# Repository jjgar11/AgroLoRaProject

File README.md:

# Proyecto de Lineas y Antenas 2025-1

## Introduccion

Aca se presenta el codigo necesario para los modulos ESP32 que se encargan de la recepcion y transmision usando dos modulos LoRa.

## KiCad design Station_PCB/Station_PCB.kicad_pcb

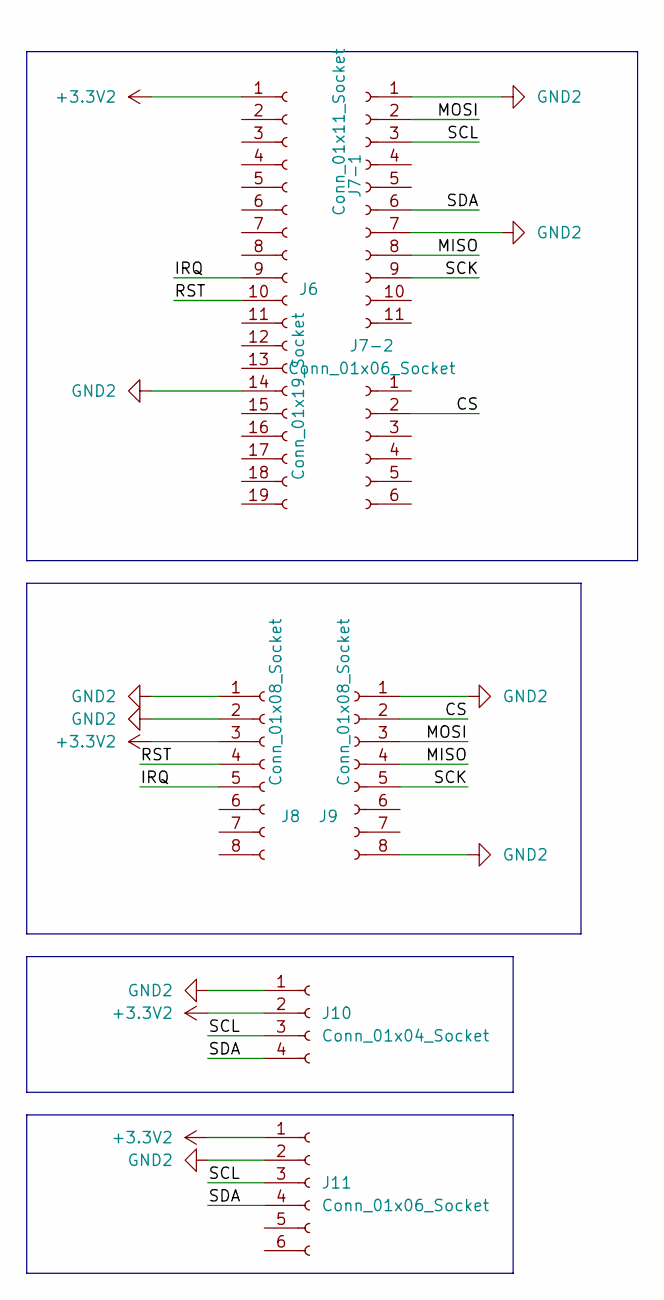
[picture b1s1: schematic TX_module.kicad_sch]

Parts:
J6: Conn_01x19_Socket; PinSocket_1x19_P2.54mm_Vertical
J7-1: Conn_01x11_Socket; PinSocket_1x11_P2.54mm_Vertical
J7-2, J11: Conn_01x06_Socket; PinSocket_1x06_P2.54mm_Vertical
J8, J9: Conn_01x08_Socket; PinSocket_1x08_P2.54mm_Vertical
J10: Conn_01x04_Socket; PinSocket_1x04_P2.54mm_Vertical

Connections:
+3.3V2: J6.1, J8.3, J10.2, J11.1
/TX_module/CS: J7-2.2, J9.2
/TX_module/IRQ: J6.9, J8.5
/TX_module/MISO: J7-1.8, J9.4
/TX_module/MOSI: J7-1.2, J9.3
/TX_module/RST: J6.10, J8.4
/TX_module/SCK: J7-1.9, J9.5
/TX_module/SCL: J7-1.3, J10.3, J11.3
/TX_module/SDA: J7-1.6, J10.4, J11.4
GND2: J6.14, J7-1.1, J7-1.7, J8.1, J8.2, J9.1, J9.8, J10.1, J11.2

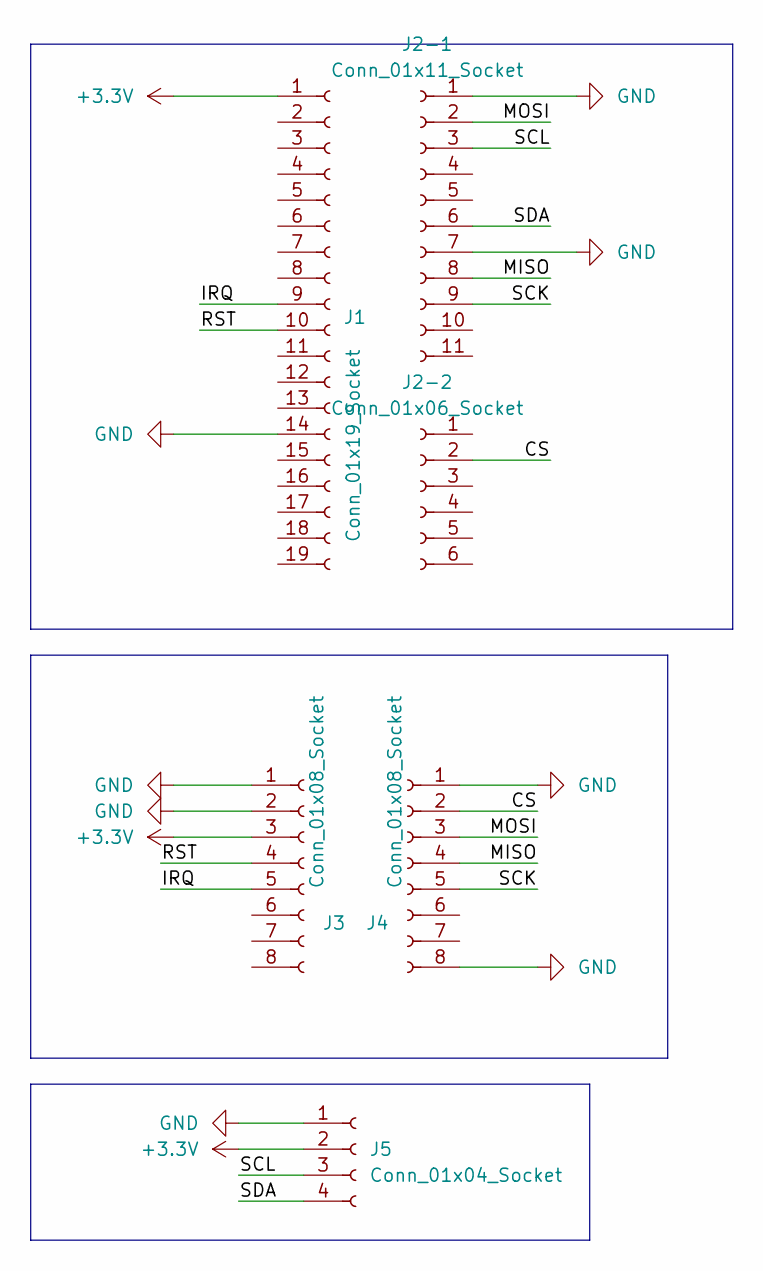
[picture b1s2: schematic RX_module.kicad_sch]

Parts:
J1: Conn_01x19_Socket; PinSocket_1x19_P2.54mm_Vertical
J2-1: Conn_01x11_Socket; PinSocket_1x11_P2.54mm_Vertical
J2-2: Conn_01x06_Socket; PinSocket_1x06_P2.54mm_Vertical
J3, J4: Conn_01x08_Socket; PinSocket_1x08_P2.54mm_Vertical
J5: Conn_01x04_Socket; PinSocket_1x04_P2.54mm_Vertical

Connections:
+3.3V: J1.1, J3.3, J5.2
/RX_module/CS: J2-2.2, J4.2
/RX_module/IRQ: J1.9, J3.5
/RX_module/MISO: J2-1.8, J4.4
/RX_module/MOSI: J2-1.2, J4.3
/RX_module/RST: J1.10, J3.4
/RX_module/SCK: J2-1.9, J4.5
/RX_module/SCL: J2-1.3, J5.3
/RX_module/SDA: J2-1.6, J5.4
GND: J1.14, J2-1.1, J2-1.7, J3.1, J3.2, J4.1, J4.8, J5.1

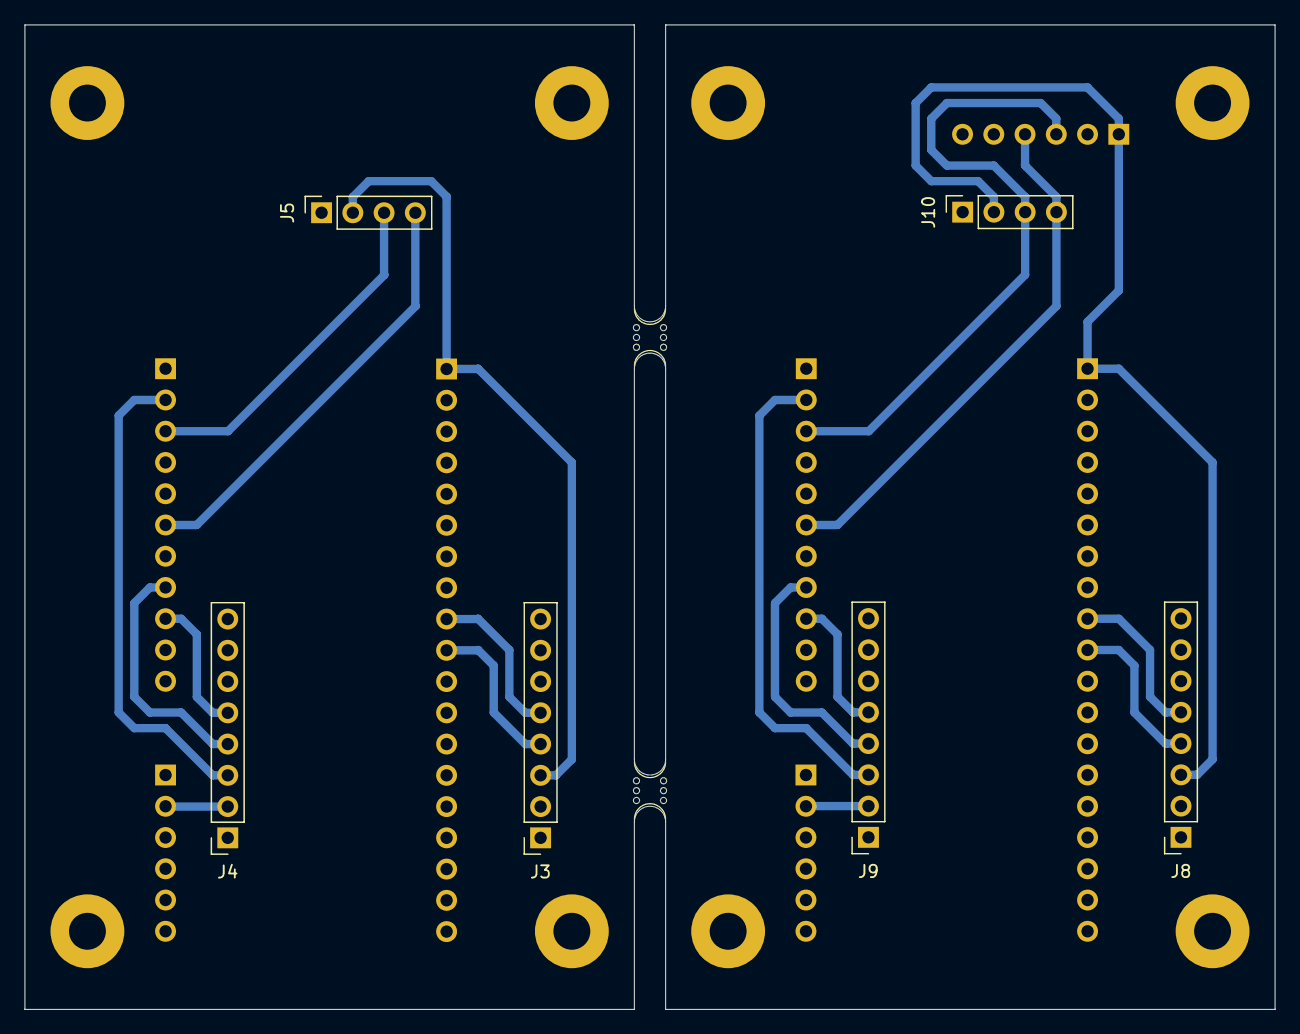
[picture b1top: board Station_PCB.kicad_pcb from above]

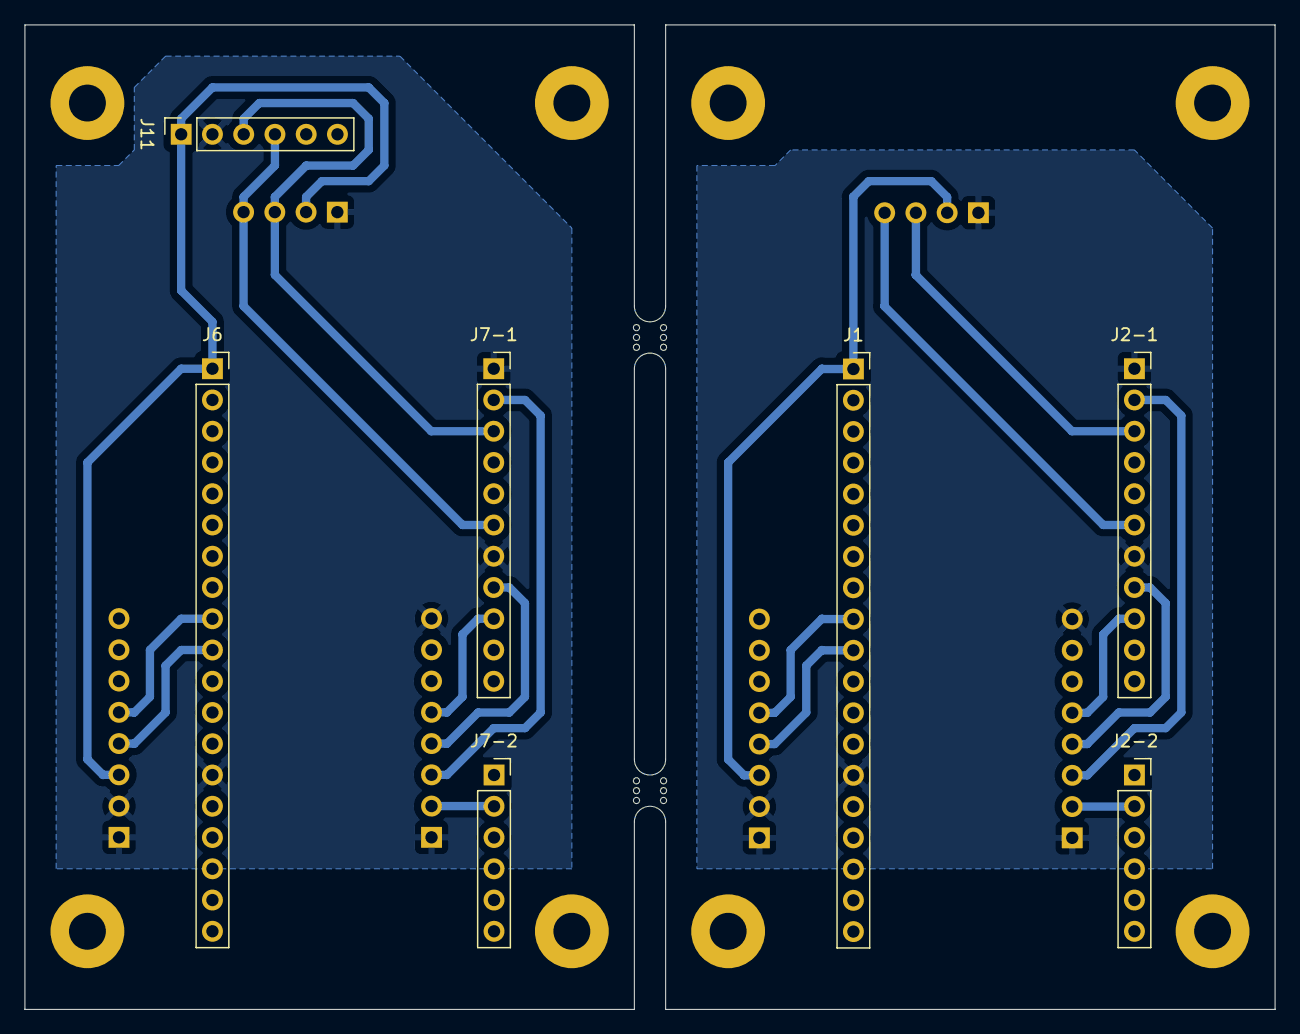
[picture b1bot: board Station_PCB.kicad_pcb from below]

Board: 2 copper layers, 101.6 x 80.0 mm, 15 parts (7 on the bottom side), 20 nets.

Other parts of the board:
mouse-bite-2.54mm-slot, mouse-bite-2.54mm-slot#2: VAL**; mouse-bite-2.54mm-slot

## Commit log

2025-06-17 Codigo inicial segmentado para el funcionamiento de cada uno de los sensores, pantalla y modulos de transmision y recepcion.
2025-06-17 Adicion de codigo separado para los modulos de RX y TX
2025-06-17 Correccion de visualizacion de datos en RX
2025-06-17 Pasar LORA_FREQ como definicion desde config.h
2025-06-17 Agregar timestamp para evitar leer paquetes duplicados
2025-06-17 Segmentacion de data recibida para mejorar comprension
2025-06-17 Modificar ID del paquete, imprimirlo
2025-06-17 Cambiar formateo de paquete para envio y activar deep sleep en TX
2025-06-17 Mover archivos a carpeta compatible
2025-06-17 Arreglar imports
2025-06-17 Agregar links para facilitar compilacion en Arduino IDE
2025-06-19 Mover todo el codigo de arduino a una carpeta propia
2025-06-19 Creacion del servidor basico con Flask
2025-06-20 Cambio de links simbolicos para que rastreen todos los cambios hechos en common/
2025-06-20 Move Arduino imports
2025-06-20 Mover utils a un path valido donde arduino lo reconozca
2025-06-20 Agregar metodos para conexion wifi y envio de datos al servidor
2025-06-20 Crear config_template que no exponga las credenciales reales de conexion
2025-06-22 Mover claves y variables privadas a un archivo aparte
2025-07-16 Mejorar comunicacion entre modulos lora y mejorar el paquete enviado al servidor
2025-07-16 Agrega visualizacion basica en localhost:5000/data
2025-07-17 Permite visualizacion de datos en tabla sencilla de html
2025-07-17 Final PCB design
2025-07-17 Corregir parametros de pistas y agregar mounthing holes
2025-07-18 Mejora placa y la deja en una sola cara para impresion
2025-07-18 Mover a cara trasera para impresion
2025-07-19 Modificar conexion a wifi para que no bloquee recepcion de datos
2025-07-19 Agregar influxDB para visualizar en Grafana
2025-07-19 Arreglar envio de datos a influxdb
